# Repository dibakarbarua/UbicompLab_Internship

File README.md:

raspberrypi-sensing
===================

Summer Internship, 2013. MUC Lab- IIIT Delhi.

Hey Guys

This is my Repository for my Summer Project which I did at the
Mobile and Ubiquitous Computing Group, IIIT Delhi in Summer, 2013.
I interfaced various sensors on various protocols on the Raspberry Pi
and made an extension board for the fronend to a Cloud-based Sensor
data acquisition system called SENSORACT.

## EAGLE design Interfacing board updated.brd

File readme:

Hey Guys

This is my Repository for my Summer Project which I did at the
Mobile and Ubiquitous Computing Group, IIIT Delhi in Summer, 2013.
I interfaced various sensors on various protocols on the Raspberry Pi
and made an extension board for the fronend to a Cloud-based Sensor
data acquisition system called SENSORACT.

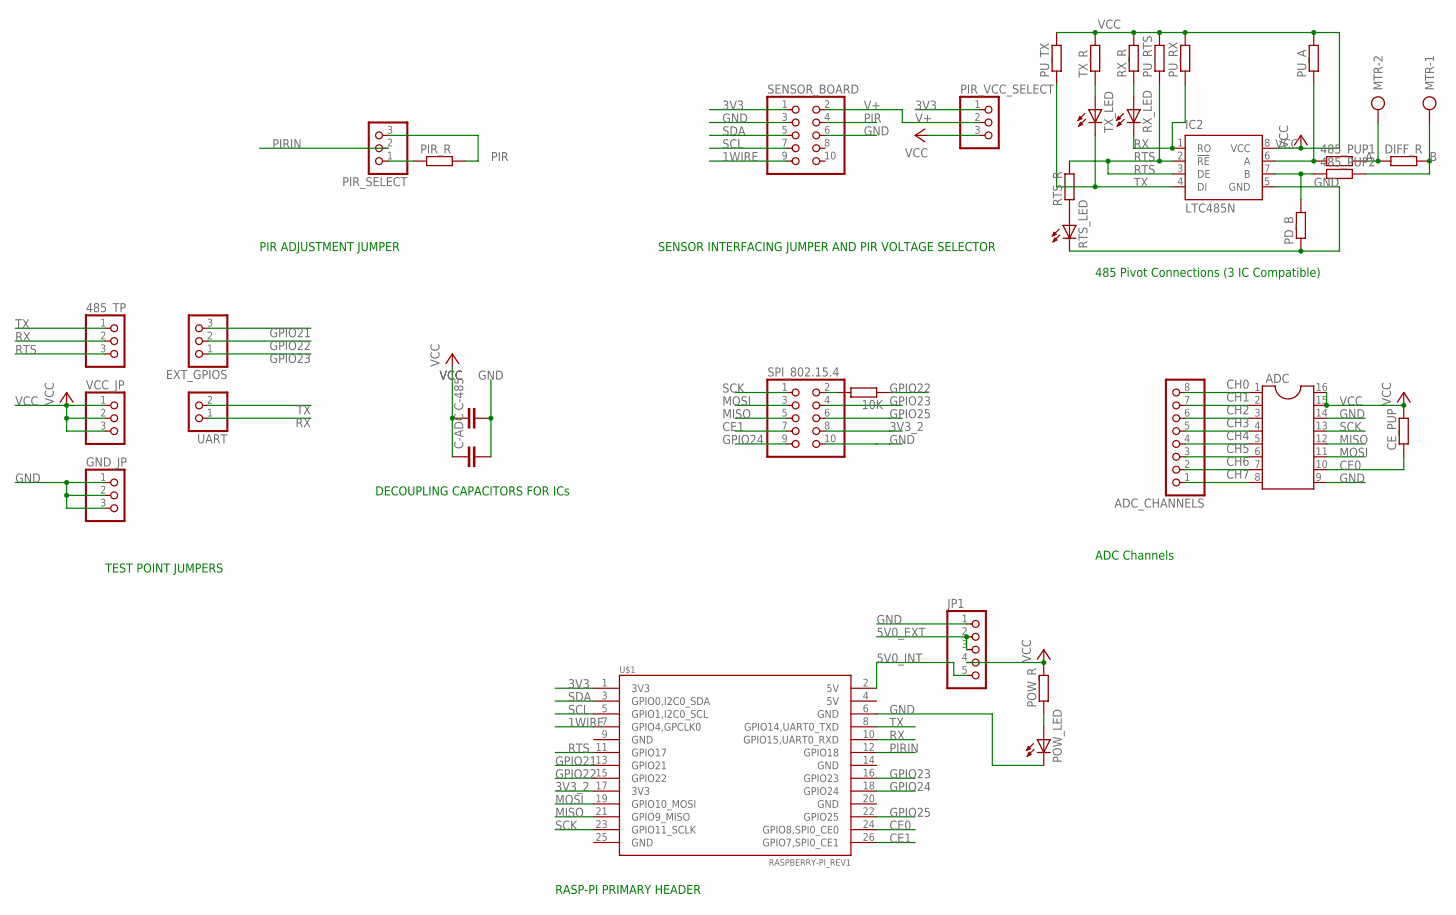
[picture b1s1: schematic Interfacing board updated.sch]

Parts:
10K, 485_PUP1, 485_PUP2: R-EU_R0603; R0603
485_TP: PINHD-1X3/90; 1X03/90
ADC: DIL16
ADC_CHANNELS: PINHD-1X8/90; 1X08/90
C-485: C-EU025-025X050; C025-025X050
C-ADC: C-EU025-025X050; C025-025X050
CE_PUP: R-EU_R0603; R0603
DIFF_R: R-EU_R0603; R0603
EXT_GPIOS: PINHD-1X3/90; 1X03/90
GND_JP: PINHD-1X3/90; 1X03/90
IC2: LTC485N; DIL08
JP1: PINHD-1X5; 1X05
MTR: AK500/2-H
PD_B: R-EU_R0603; R0603
PIR_R: R-EU_R0603; R0603
PIR_SELECT: PINHD-1X3/90; 1X03/90
PIR_VCC_SELECT: PINHD-1X3/90; 1X03/90
POW_LED: LEDCHIPLED_0805; CHIPLED_0805
POW_R: R-EU_R0603; R0603
PU_A: R-EU_R0603; R0603
PU_RTS: R-EU_R0603; R0603
PU_RX: R-EU_R0603; R0603
PU_TX: R-EU_R0603; R0603
RTS_LED: LEDCHIPLED_0805; CHIPLED_0805
RTS_R: R-EU_R0603; R0603
RX_LED: LEDCHIPLED_0805; CHIPLED_0805
RX_R: R-EU_R0603; R0603
SENSOR_BOARD: PINHD-2X5/90; 2X05/90
SPI_802.15.4: PINHD-2X5/90; 2X05/90
TX_LED: LEDCHIPLED_0805; CHIPLED_0805
TX_R: R-EU_R0603; R0603
U$1: RASPBERRY-PI_REV1
UART: PINHD-1X2; 1X02
VCC_JP: PINHD-1X3/90; 1X03/90

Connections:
1WIRE: SENSOR_BOARD.9, U$1.7 (GPIO4,GPCLK0)
3V3: PIR_VCC_SELECT.1, SENSOR_BOARD.1, U$1.1 (3V3)
3V3_2: SPI_802.15.4.8, U$1.17 (3V3)
5V0_EXT: JP1.2, JP1.3
5V0_INT: JP1.5, U$1.2 (5V)
A: 485_PUP1.2, DIFF_R.1, MTR.2
B: 485_PUP2.2, DIFF_R.2, MTR.1
CE0: ADC.10, CE_PUP.1, U$1.24 (GPIO8,SPI0_CE0)
CE1: SPI_802.15.4.7, U$1.26 (GPIO7,SPI0_CE1)
CH0: ADC.1, ADC_CHANNELS.8
CH1: ADC.2, ADC_CHANNELS.7
CH2: ADC.3, ADC_CHANNELS.6
CH3: ADC.4, ADC_CHANNELS.5
CH4: ADC.5, ADC_CHANNELS.4
CH5: ADC.6, ADC_CHANNELS.3
CH6: ADC.7, ADC_CHANNELS.2
CH7: ADC.8, ADC_CHANNELS.1
GND: ADC.9, ADC.14, C-485.2, C-ADC.2, GND_JP.1, GND_JP.2, GND_JP.3, IC2.5 (GND), JP1.1, PD_B.1, POW_LED.C, RTS_LED.C, SENSOR_BOARD.3, SENSOR_BOARD.6, SPI_802.15.4.10, U$1.6 (GND)
GPIO21: EXT_GPIOS.3, U$1.13 (GPIO21)
GPIO22: 10K.1, EXT_GPIOS.2, U$1.15 (GPIO22)
GPIO23: EXT_GPIOS.1, SPI_802.15.4.4, U$1.16 (GPIO23)
GPIO24: SPI_802.15.4.9, U$1.18 (GPIO24)
GPIO25: SPI_802.15.4.6, U$1.22 (GPIO25)
MISO: ADC.12, SPI_802.15.4.5, U$1.21 (GPIO9_MISO)
MOSI: ADC.11, SPI_802.15.4.3, U$1.19 (GPIO10_MOSI)
unnamed: 485_PUP1.1, IC2.6 (A), PU_A.1
unnamed: 485_PUP2.1, IC2.7 (B), PD_B.2
unnamed: PIR_R.1, PIR_SELECT.1
unnamed: POW_LED.A, POW_R.1
unnamed: RTS_LED.A, RTS_R.1
unnamed: 10K.2, SPI_802.15.4.2
PIR: PIR_R.2, PIR_SELECT.3, SENSOR_BOARD.4
PIRIN: PIR_SELECT.2, U$1.12 (GPIO18)
RTS: 485_TP.3, IC2.2 (!RE), IC2.3 (DE), PU_RTS.1, RTS_R.2, U$1.11 (GPIO17)
RX: 485_TP.2, IC2.1 (RO), PU_RX.1, RX_LED.C, U$1.10 (GPIO15,UART0_RXD), UART.1
RX_R: RX_LED.A, RX_R.1
SCK: ADC.13, SPI_802.15.4.1, U$1.23 (GPIO11_SCLK)
SCL: SENSOR_BOARD.7, U$1.5 (GPIO1,I2C0_SCL)
SDA: SENSOR_BOARD.5, U$1.3 (GPIO0,I2C0_SDA)
TX: 485_TP.1, IC2.4 (DI), PU_TX.1, TX_LED.C, U$1.8 (GPIO14,UART0_TXD), UART.2
TX_R: TX_LED.A, TX_R.1
V+: PIR_VCC_SELECT.2, SENSOR_BOARD.2
VCC: ADC.15, ADC.16, C-485.1, C-ADC.1, CE_PUP.2, IC2.8 (VCC), JP1.4, PIR_VCC_SELECT.3, POW_R.2, PU_A.2, PU_RTS.2, PU_RX.2, PU_TX.2, RX_R.2, TX_R.2, VCC_JP.1, VCC_JP.2, VCC_JP.3

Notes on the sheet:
ADC Channels
485 Pivot Connections (3 IC Compatible)
SENSOR INTERFACING JUMPER AND PIR VOLTAGE SELECTOR
PIR ADJUSTMENT JUMPER
DECOUPLING CAPACITORS FOR ICs
TEST POINT JUMPERS
RASP-PI PRIMARY HEADER

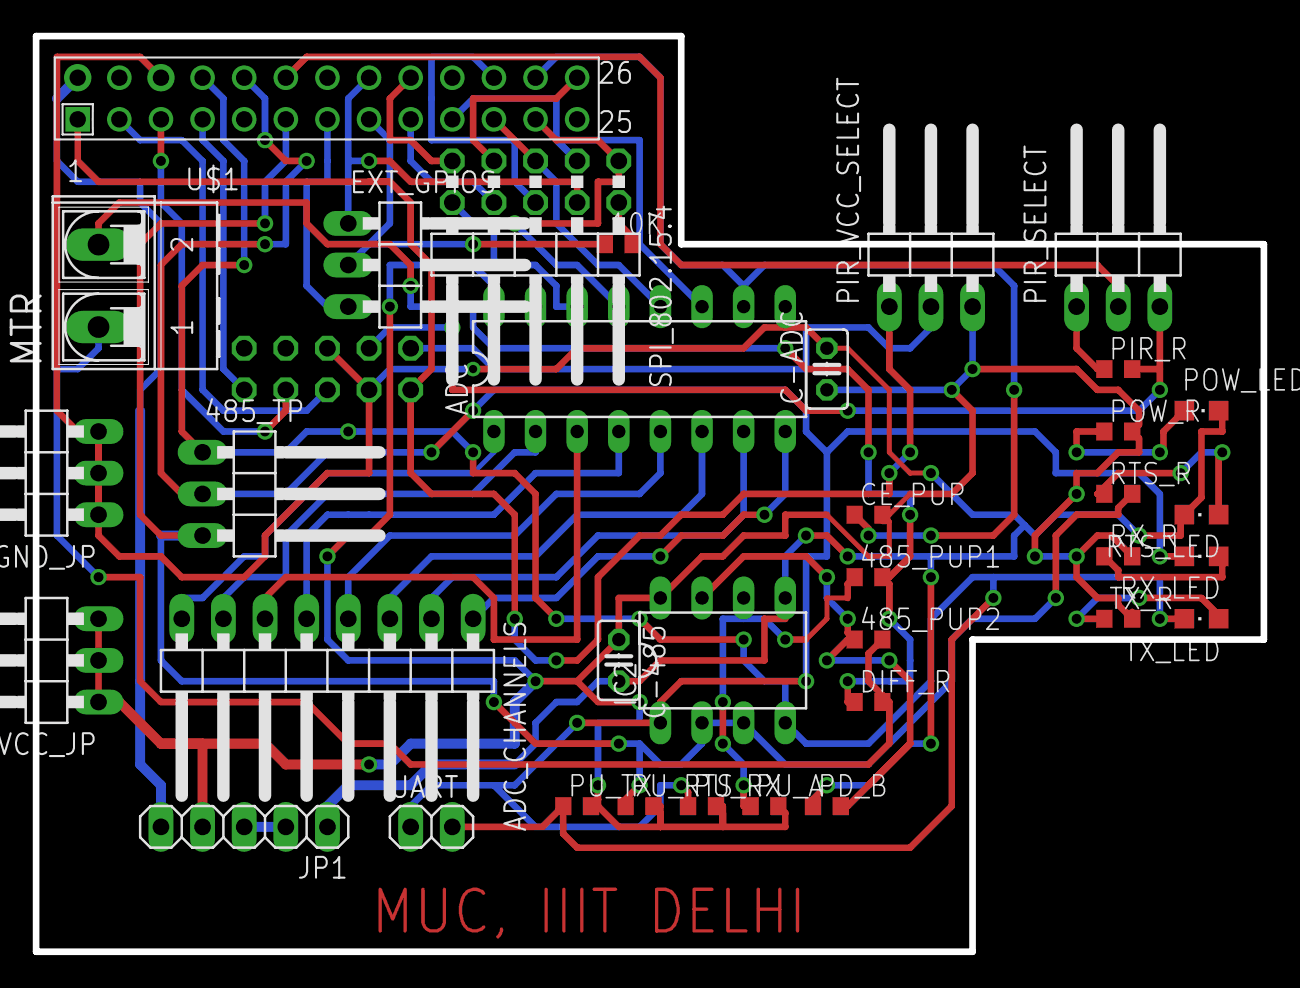
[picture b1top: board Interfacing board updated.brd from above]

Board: 2 copper layers, 74.9 x 55.9 mm, 36 parts (1 on the bottom side), 43 nets.

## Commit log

2014-02-06 Final Commit with Codes
2014-02-06 Final Commit
